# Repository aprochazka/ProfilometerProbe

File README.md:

# Profilometer Probe
## Device was created as part of a bachelor's thesis at BUT VUT 2022/2023 named Probe for Determining the Surface Condition of Small Diameter Barrels 
## Detailed description of device design and implementation is inside thesis  

## Hardware

### Models

- All 3D printable models are located inside Models folder
- Models are designed to be printed with standard 2mm layer height
- When slicing be sure to print outer walls first to make print more accurate

### Assembly 

- All screws are size M3
- Assembly should be done accordingly  

### PCB

- PCB should be two sided with 1.6mm width
- Design files are created in KiCad

### Components

- Development board: Nucleo L432KC
- Camera: ArduCam mini 5MP Plus
- Distance sensor: Pimoroni LV53L1X
- Complete list of components and connectors for probe can be found inside HW/Parts.md

## Firmware for profilometer probe

### Build

- Build using Makefile inside Firmware folder (dependency: arm-none-eabi)
- Flash onto hardware using flash option for make command `$ make flash`

### Usage

- Connect probe to pc using usb c cable and firmware will start sending sending data automatically

### Documentation

- Create documentation using 'doc' option of Makefile '$ make doc' 

## Software for receiving data

### Build

- Build using Makefile inside Receiver folder

### Usage

- Has to be run with sudo permissions to correctly access USB CDC port.
- '$ sudo ./main -p <name of the port> [-s Save received jpeg to files] [-r Print raw received CDC data to standard output]'
- Prefer running with optional -s command for ability to inspect already captured images 

### Documentation

- Create documentation using 'doc' option of Makefile '$ make doc' 

### TODO

- Process image and filter only laser line from it
- Use precessed data to determine depth or height of irregularities

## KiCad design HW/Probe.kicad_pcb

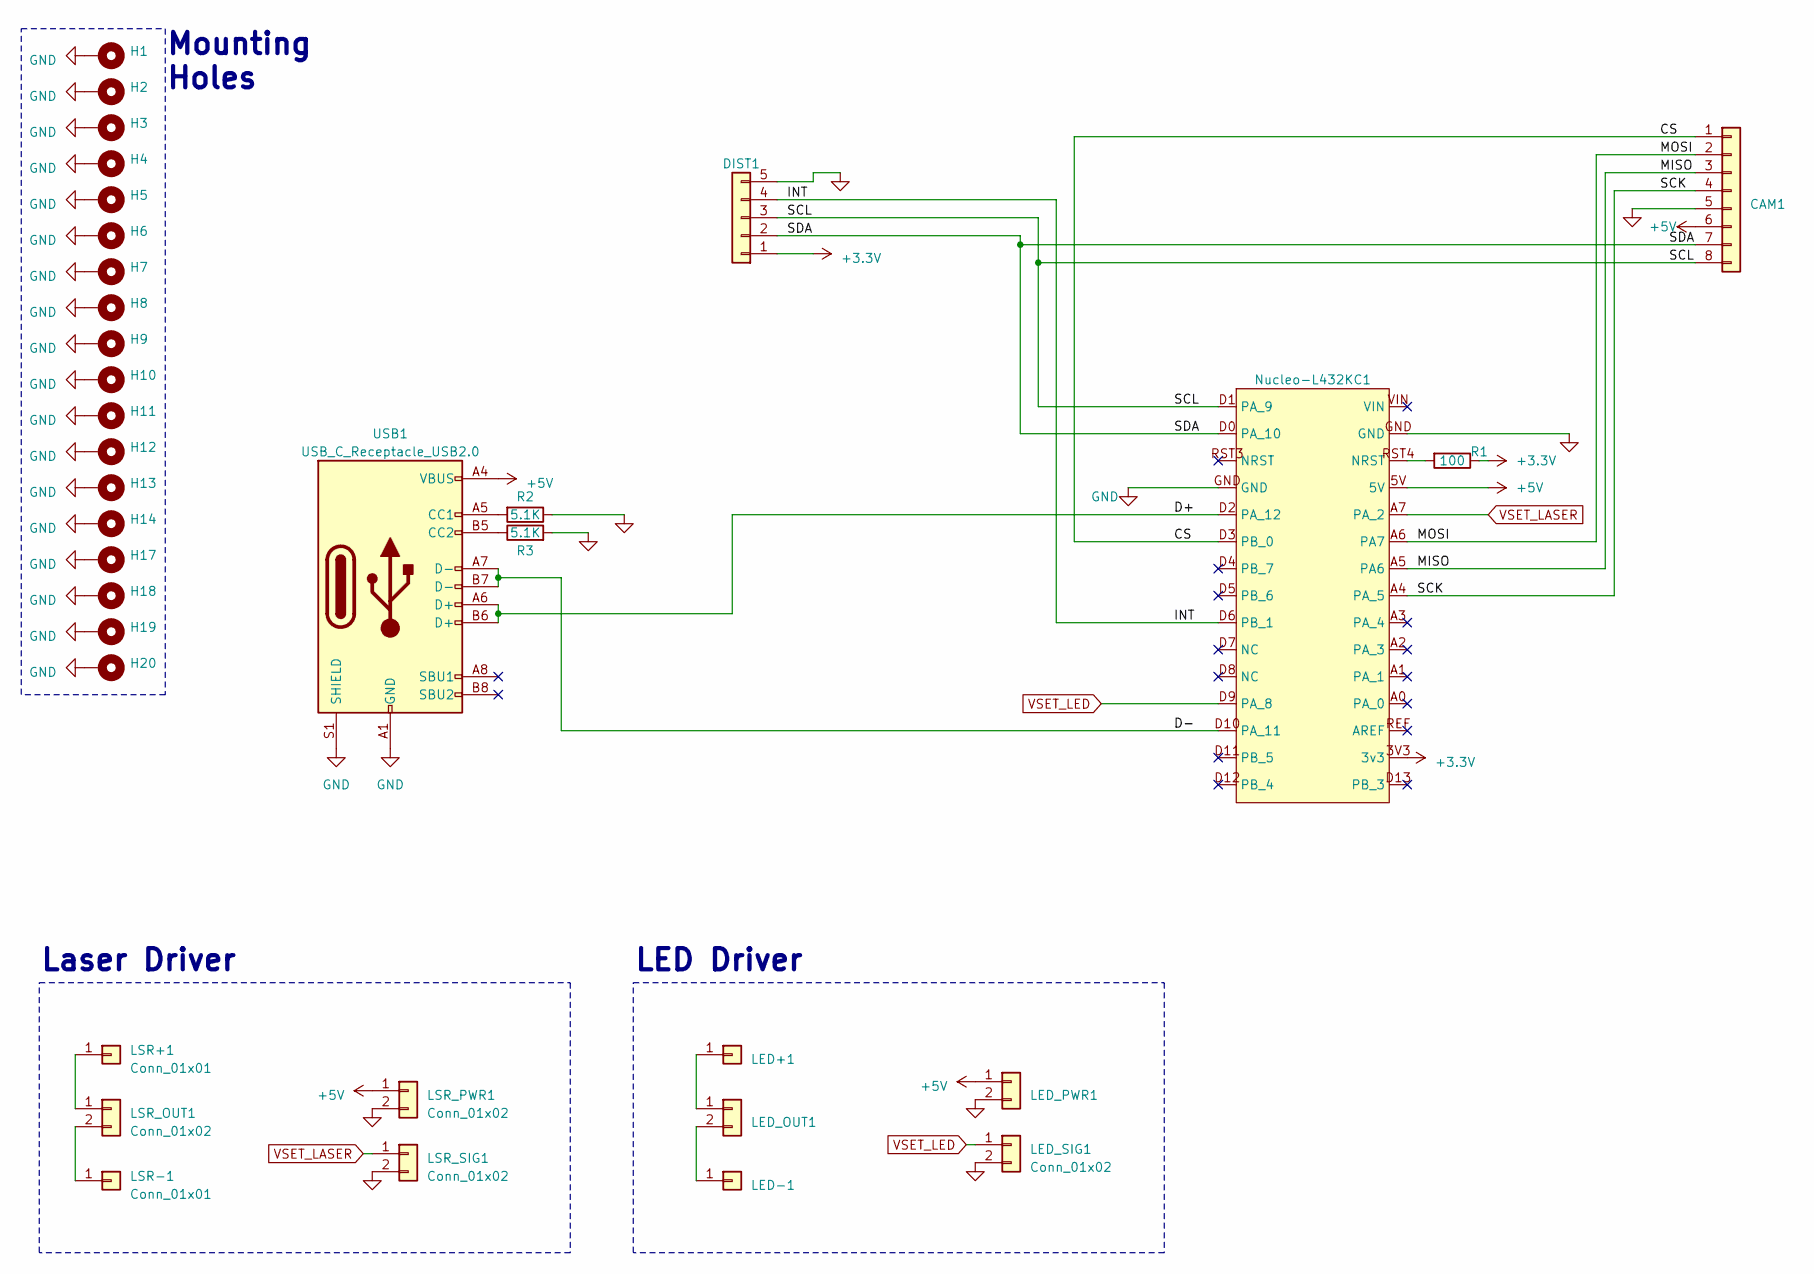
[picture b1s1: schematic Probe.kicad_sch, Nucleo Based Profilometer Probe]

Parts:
CAM1: Conn_01x08; PinSocket_1x08_P2.54mm_Vertical
DIST1: Conn_01x05; PinSocket_1x05_P2.54mm_Vertical
H1, H2, H3, H4, H5, H6, H7, H8, H9, H10, H11, H12, H13, H14, H17, H18, H19, H20: MountingHole_Pad; MountingHole_3.2mm_M3_Pad_Via
LED+1: Conn_01x01; PinHeader_1x01_P2.54mm_Vertical
LED-1: Conn_01x01; PinHeader_1x01_P2.54mm_Vertical
LED_OUT1: Conn_01x02; PinHeader_1x02_P2.54mm_Vertical
LED_PWR1: Conn_01x02; PinHeader_1x02_P2.54mm_Vertical
LED_SIG1: Conn_01x02; PinHeader_1x02_P2.54mm_Vertical
LSR+1: Conn_01x01; PinHeader_1x01_P2.54mm_Vertical
LSR-1: Conn_01x01; PinHeader_1x01_P2.54mm_Vertical
LSR_OUT1: Conn_01x02; PinHeader_1x02_P2.54mm_Vertical
LSR_PWR1: Conn_01x02; PinHeader_1x02_P2.54mm_Vertical
LSR_SIG1: Conn_01x02; PinHeader_1x02_P2.54mm_Vertical
Nucleo-L432KC1: MODULE_NUCLEO-L432KC
R1: 100; R_0603_1608Metric
R2, R3: 5.1K; R_0603_1608Metric
USB1: USB_C_Receptacle_USB2.0; USB_C_Receptacle_HRO_TYPE-C-31-M-12

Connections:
+3.3V: DIST1.1, Nucleo-L432KC1.3V3 (3v3), R1.1
+5V: CAM1.6, LED_PWR1.1, LSR_PWR1.1, Nucleo-L432KC1.5V, USB1.A4 (VBUS), USB1.A9 (VBUS), USB1.B4 (VBUS), USB1.B9 (VBUS)
/CS: CAM1.1, Nucleo-L432KC1.D3 (PB_0)
/D+: Nucleo-L432KC1.D2 (PA_12), USB1.A6 (D+), USB1.B6 (D+)
/D-: Nucleo-L432KC1.D10 (PA_11), USB1.A7 (D-), USB1.B7 (D-)
/INT: DIST1.4, Nucleo-L432KC1.D6 (PB_1)
/MISO: CAM1.3, Nucleo-L432KC1.A5 (PA6)
/MOSI: CAM1.2, Nucleo-L432KC1.A6 (PA7)
/SCK: CAM1.4, Nucleo-L432KC1.A4 (PA_5)
/SCL: CAM1.8, DIST1.3, Nucleo-L432KC1.D1 (PA_9)
/SDA: CAM1.7, DIST1.2, Nucleo-L432KC1.D0 (PA_10)
GND: CAM1.5, DIST1.5, H1.1, H2.1, H3.1, H4.1, H5.1, H6.1, H7.1, H8.1, H9.1, H10.1, H11.1, H12.1, H13.1, H14.1, H17.1, H18.1, H19.1, H20.1, LED_PWR1.2, LED_SIG1.2, LSR_PWR1.2, LSR_SIG1.2, Nucleo-L432KC1.GND, R2.1, R3.2, USB1.A1 (GND), USB1.A12 (GND), USB1.B1 (GND), USB1.B12 (GND), USB1.S1 (SHIELD)
unnamed: LED+1.1, LED_OUT1.1
unnamed: LED-1.1, LED_OUT1.2
unnamed: LSR+1.1, LSR_OUT1.1
unnamed: LSR-1.1, LSR_OUT1.2
unnamed: Nucleo-L432KC1.RST4 (NRST), R1.2
unnamed: R2.2, USB1.A5 (CC1)
unnamed: R3.1, USB1.B5 (CC2)
VSET_LASER: LSR_SIG1.1, Nucleo-L432KC1.A7 (PA_2)
VSET_LED: LED_SIG1.1, Nucleo-L432KC1.D9 (PA_8)

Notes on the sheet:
Laser Driver
Mounting Holes
LED Driver

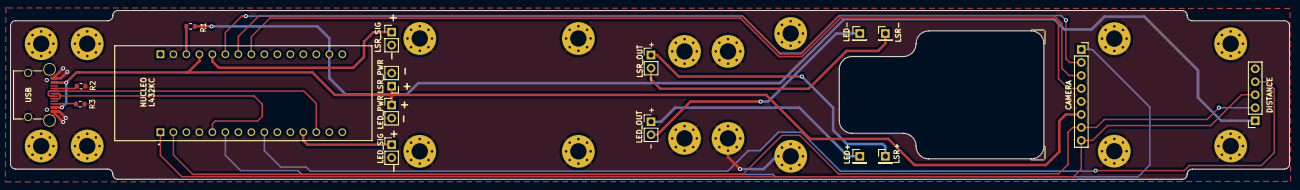
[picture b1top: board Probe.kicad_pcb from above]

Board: 2 copper layers, 250.0 x 33.0 mm, 35 parts (0 on the bottom side), 21 nets.

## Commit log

2023-02-19 sending sequences of jpeg
2023-02-19 add parts markdown file
2023-02-19 about 20% of pictures are not corrupted
2023-02-19 Edit README
2023-02-20 add test script
2023-02-23 Error in makefile
2023-02-23 uncomment makefile
2023-02-28 buildable with cmake
2023-03-01 add TinyUSB
2023-03-02 Move TinyUSB to root and try to implement cdc_msc
2023-03-22 add block scheme of device
2023-03-24 add block scheme of device to readme
2023-03-27 non working uvc example
2023-03-30 add receiver application for CDC video transfer
2023-04-04 Camera progress
2023-04-06 Sending pictures - problems with cdc testing using receiver app
2023-04-07 First fully working camera capture, transfer and receive!
2023-04-08 Increase resolution, decrease send interval
2023-04-09 More optimalizations and multithreading - 1FPS
2023-04-10 Auto config, no need to init before each capture, 320x240 cca 5fps
2023-04-13 720p resolution
2023-04-16 Add distance sensor, README update in next commit
2023-04-18 Create probe pcb
2023-04-18 Update footprints for cam and distance sensor
2023-04-19 Update PCB
2023-04-19 Add title to sheets
2023-04-19 Update parts list
2023-04-20 Change USB footprint, label PCB
2023-04-20 Remove user files
2023-05-09 Push local changes for complete and functioning probe
2023-05-09 Add stl files of device
2023-05-09 Update parts
2023-05-09 update image name
2023-05-09 Update documentation
